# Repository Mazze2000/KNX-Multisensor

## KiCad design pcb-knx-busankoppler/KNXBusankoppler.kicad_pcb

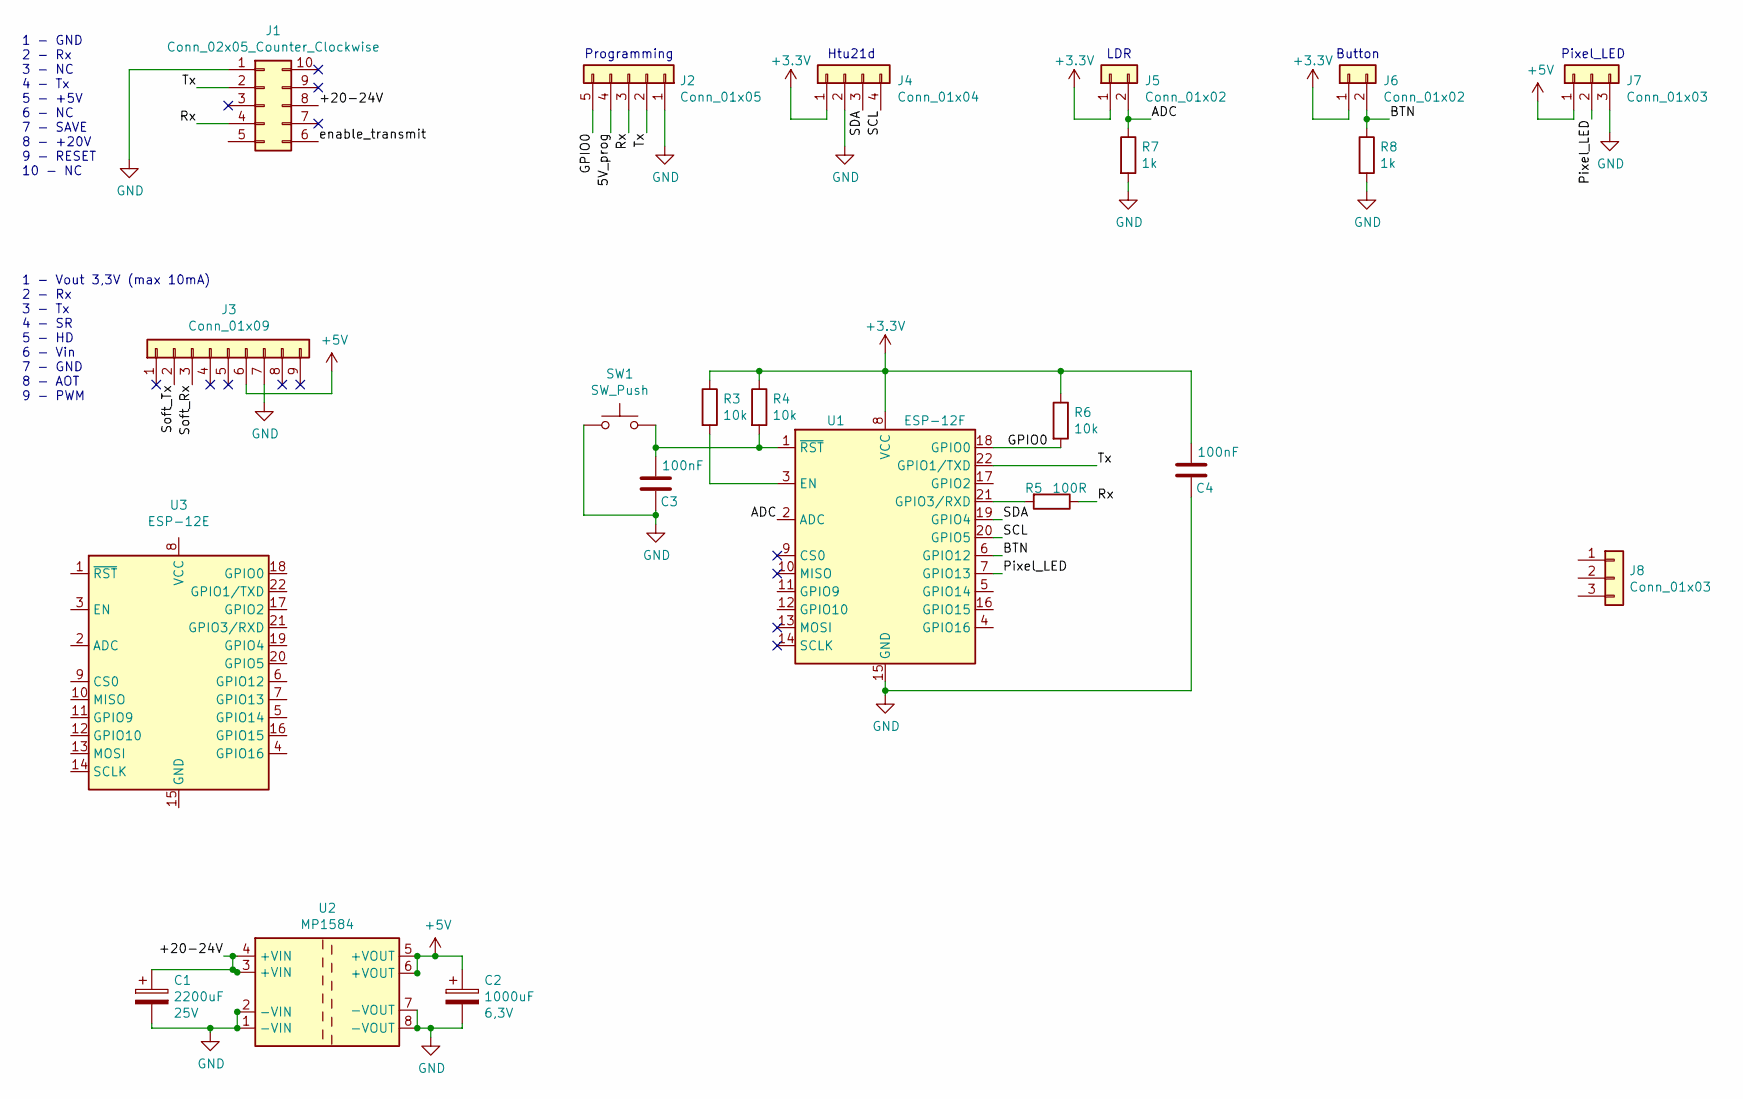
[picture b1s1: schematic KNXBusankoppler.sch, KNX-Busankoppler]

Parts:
C1: 2200uF; CP_Radial_D10.0mm_P5.00mm; Voltage 25V
C2: 1000uF; CP_Radial_D8.0mm_P3.80mm; Voltage 6,3V
C3, C4: 100nF; C_0603_1608Metric_Pad1.05x0.95mm_HandSolder
J1: Conn_02x05_Counter_Clockwise; PinHeader_2x05_P2.54mm_Vertical
J2: Conn_01x05; PinHeader_1x05_P2.54mm_Vertical
J3: Conn_01x09; Winsen_MH-Z19B
J4: Conn_01x04; PinHeader_1x04_P2.54mm_Vertical
J5, J6: Conn_01x02; PinHeader_1x02_P2.54mm_Vertical
J7: Conn_01x03; PinHeader_1x03_P2.54mm_Vertical
J8: Conn_01x03; PinHeader_1x03_P1.27mm_Vertical
R3, R4, R6: 10k; C_0603_1608Metric_Pad1.05x0.95mm_HandSolder
R5: 100R; C_0603_1608Metric_Pad1.05x0.95mm_HandSolder
R7, R8: 1k; C_0603_1608Metric_Pad1.05x0.95mm_HandSolder
SW1: SW_Push; SW_SPST_CK_RS282G05A3
U1: ESP-12F; ESP-12E
U2: MP1584
U3: ESP-12E; ESP-01M

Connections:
+3V3: C4.2, J4.1, J5.1, J6.1, R3.1, R4.1, R6.1, U1.8 (VCC)
+5V: C2.1, J3.6, J7.1, U2.5 (+VOUT), U2.6 (+VOUT)
/5V_prog: J2.4
/+20-24V: C1.1, J1.8, U2.3 (+VIN), U2.4 (+VIN)
/ADC: J5.2, R7.1, U1.2 (ADC)
/BTN: J6.2, R8.1, U1.6 (GPIO12)
/GPIO0: J2.5, R6.2, U1.18 (GPIO0)
/Pixel_LED: J7.2, U1.7 (GPIO13)
/Rx: J1.4, J2.3, R5.1
/SCL: J4.4, U1.20 (GPIO5)
/SDA: J4.3, U1.19 (GPIO4)
/Soft_Rx: J3.3
/Soft_Tx: J3.2
/Tx: J1.2, J2.2, U1.22 (GPIO1/TXD)
/enable_transmit: J1.6
GND: C1.2, C2.2, C3.1, C4.1, J1.1, J2.1, J3.7, J4.2, J7.3, R7.2, R8.2, SW1.1, U1.15 (GND), U2.1 (-VIN), U2.2 (-VIN), U2.7 (-VOUT), U2.8 (-VOUT)
unnamed: C3.2, R4.2, SW1.2, U1.1 (~RST)
unnamed: R3.2, U1.3 (EN)
unnamed: R5.2, U1.21 (GPIO3/RXD)

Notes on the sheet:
1 - GND 2 - Rx 3 - NC 4 - Tx 5 - +5V 6 - NC 7 - SAVE 8 - +20V 9 - RESET 10 - NC
Programming
Htu21d
LDR
Button
1 - Vout 3,3V (max 10mA) 2 - Rx 3 - Tx 4 - SR 5 - HD 6 - Vin 7 - GND 8 - AOT 9 - PWM
Pixel_LED

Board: 2 copper layers, 21 parts (12 on the bottom side), 10 nets, no tracks yet.

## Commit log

2021-04-08 starting Project
